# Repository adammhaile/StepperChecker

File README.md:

# StepperChecker

StepperChecker is  a stepper motor driver dev and test board, designed to be easy to build, setup, and use.
It will take any stepstick style motor driver and any Feather compatible microcontroller board.
The basic intent is to have firmware loaded that will move the motor forward or reverse based on which button is pressed, at a sped defined by the potentiometer. But, of course, the sky is the limit given the many Feather boards available.

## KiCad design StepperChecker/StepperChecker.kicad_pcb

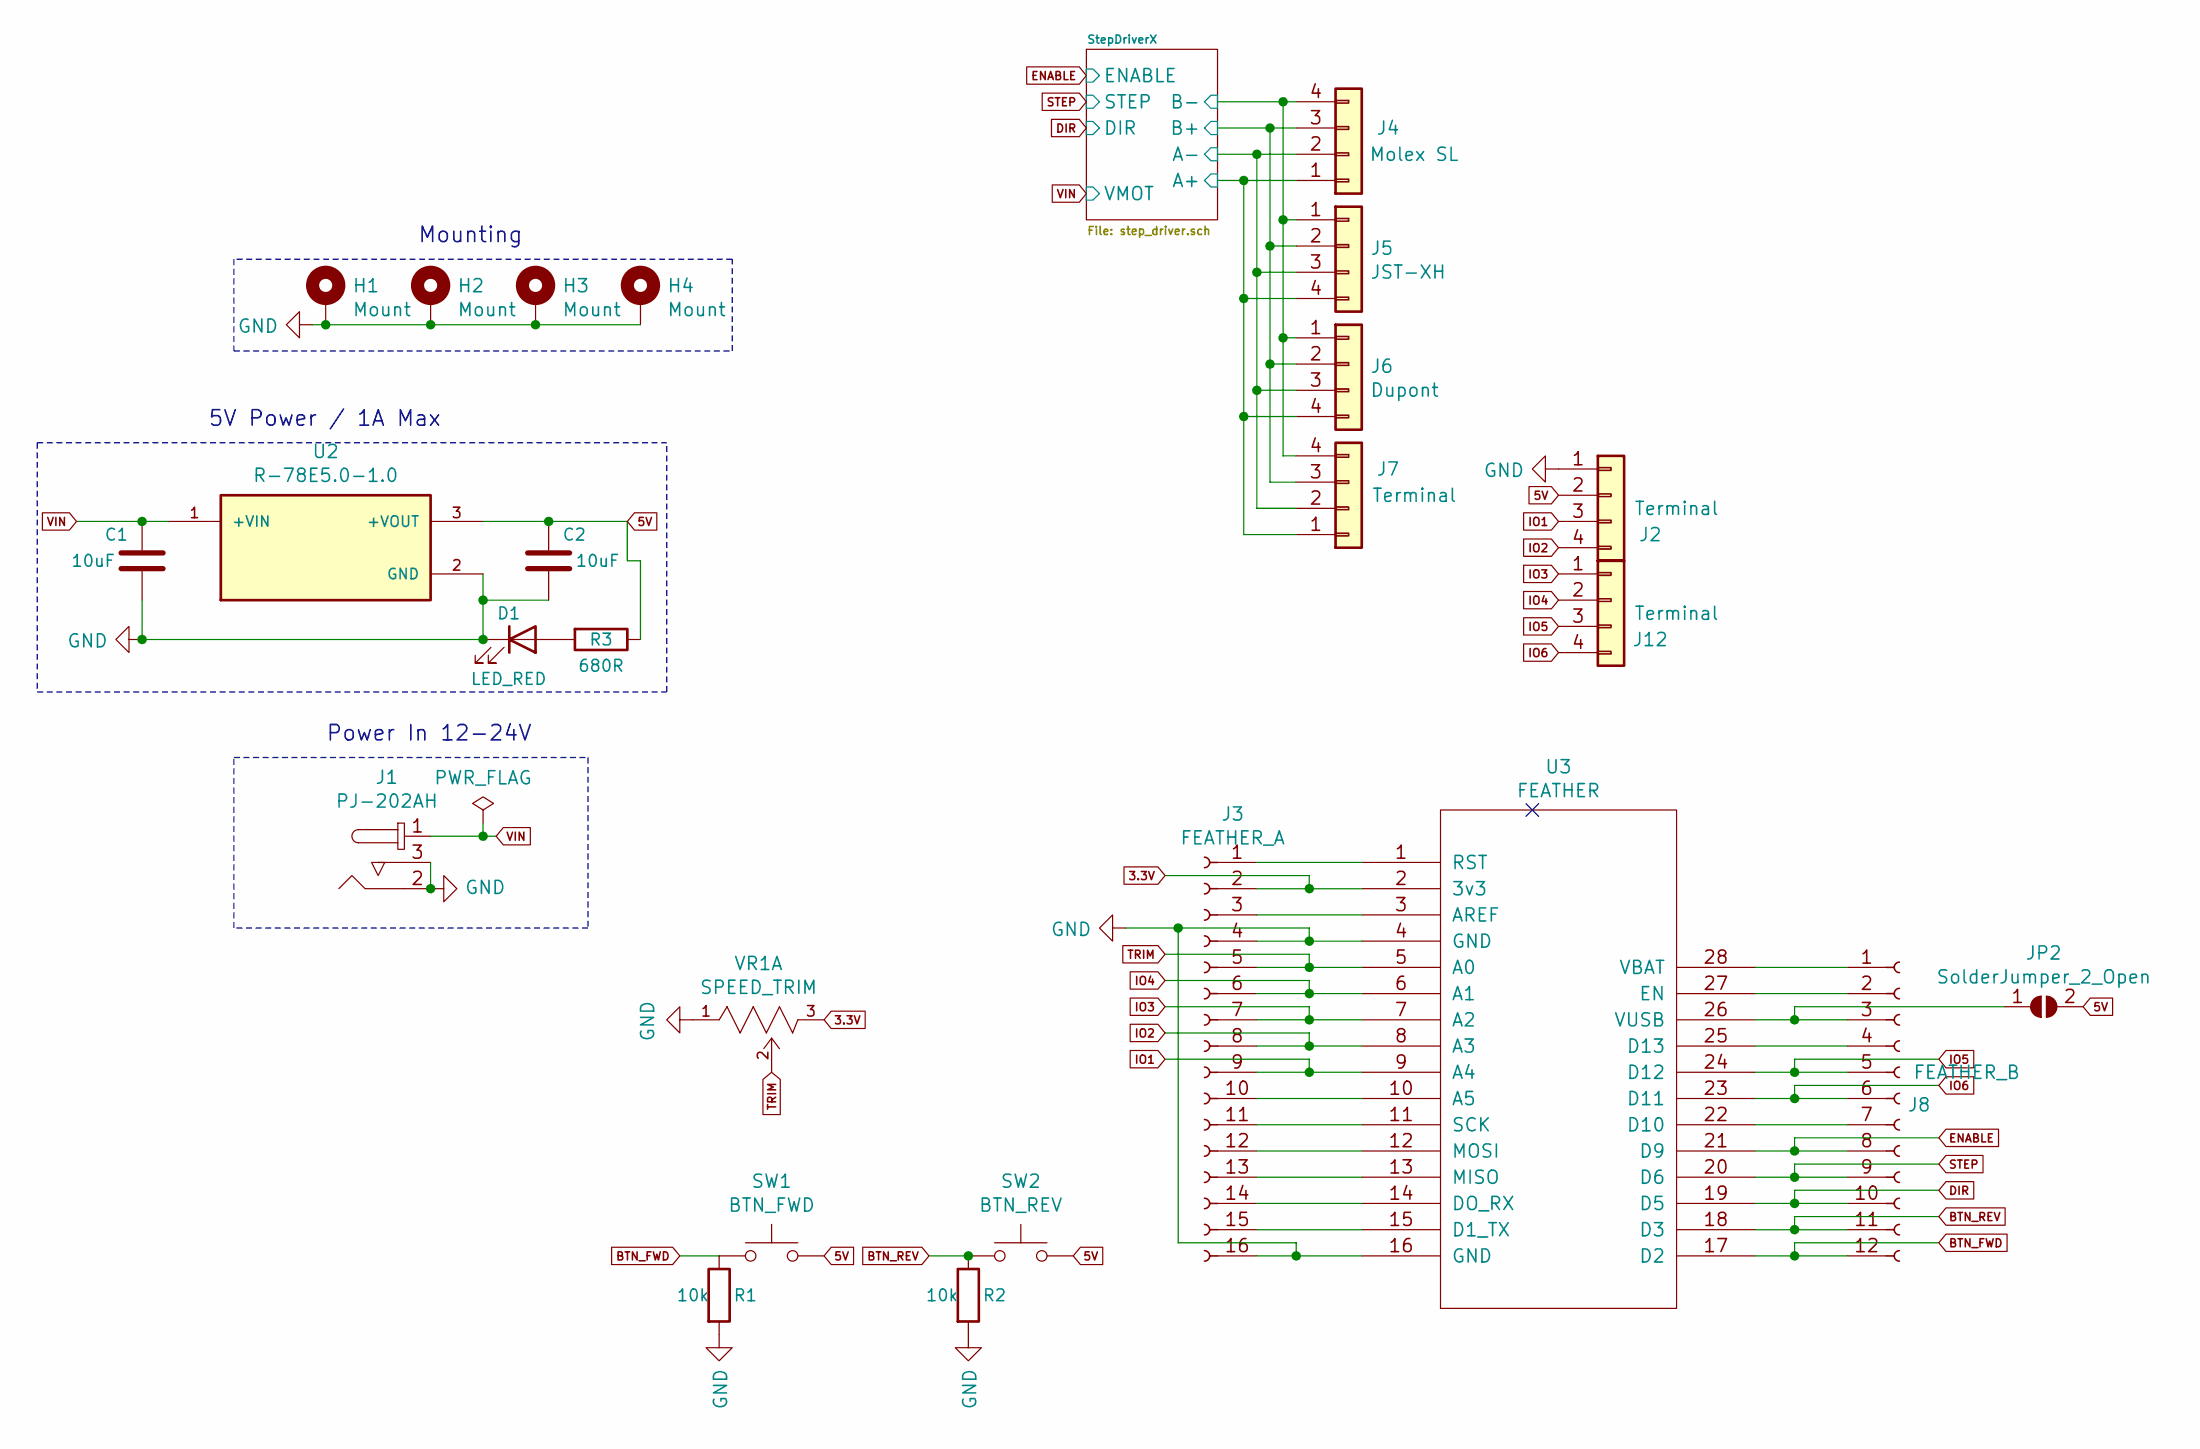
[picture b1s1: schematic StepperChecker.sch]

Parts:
C1, C2: 10uF; CP_Radial_D5.0mm_P2.00mm
D1: LED_RED; LED_D3.0mm
H1, H2, H3, H4: Mount; MountingHole_2.5mm_Pad
J1: PJ-202AH; Barrel_Jack_5.5mmODx2.1mmID_PJ-202A; MPN PJ-202AH; Digi-Key_PN CP-202AH-ND
J2, J7, J12: Terminal; TerminalBlock_Phoenix_MPT-0,5-4-2.54_1x04_P2.54mm_Horizontal
J3: FEATHER_A; PinSocket_1x16_P2.54mm_Vertical
J4: Molex SL; Molex-70543-0038-0-0-MFG
J5: JST-XH; JST_XH_B4B-XH-A_1x04_P2.50mm_Vertical
J6: Dupont; PinHeader_1x04_P2.54mm_Vertical
J8: FEATHER_B; PinSocket_1x12_P2.54mm_Vertical
JP2: SolderJumper_2_Open; SolderJumper-2_P1.3mm_Open_RoundedPad1.0x1.5mm
R1, R2: 10k; R_Axial_DIN0204_L3.6mm_D1.6mm_P7.62mm_Horizontal; MPN RC0603FR-071KL
R3: 680R; R_Axial_DIN0204_L3.6mm_D1.6mm_P7.62mm_Horizontal; MPN RC0603FR-071KL
SW1: BTN_FWD; SW_PUSH_6mm_H5mm
SW2: BTN_REV; SW_PUSH_6mm_H5mm
U2: R-78E5.0-1.0; CONV_R-78E5.0-1.0; PARTREV 6
U3: FEATHER; Adafruit_Feather
VR1: SPEED_TRIM; ALPS-RK09D1130C3W-0; mouser part number 688-RK09D1130C3W

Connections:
3.3V: J3.2, U3.2 (3v3), VR1.3
5V: C2.1, J2.2, JP2.2 (B), R3.1, SW1.2, SW2.2, U2.3 (+VOUT); also elsewhere on the board
/StepDriverX/A+: J4.1, J5.4, J6.4, J7.1; also elsewhere on the board
/StepDriverX/A-: J4.2, J5.3, J6.3, J7.2; also elsewhere on the board
/StepDriverX/B+: J4.3, J5.2, J6.2, J7.3; also elsewhere on the board
/StepDriverX/B-: J4.4, J5.1, J6.1, J7.4; also elsewhere on the board
BTN_FWD: J8.12, R1.1, SW1.1, U3.17 (D2)
BTN_REV: J8.11, R2.1, SW2.1, U3.18 (D3)
DIR: J8.10, U3.19 (D5); also elsewhere on the board
ENABLE: J8.8, U3.21 (D9); also elsewhere on the board
GND: C1.2, C2.2, D1.1 (K), H1.1, H2.1, H3.1, H4.1, J1.2, J1.3, J2.1, J3.4, J3.16, R1.2, R2.2, U2.2 (GND), U3.4 (GND), U3.16 (GND), VR1.1; also elsewhere on the board
IO1: J2.3, J3.9, U3.9 (A4)
IO2: J2.4, J3.8, U3.8 (A3)
IO3: J3.7, J12.1, U3.7 (A2)
IO4: J3.6, J12.2, U3.6 (A1)
IO5: J8.5, J12.3, U3.24 (D12)
IO6: J8.6, J12.4, U3.23 (D11)
unnamed: D1.2 (A), R3.2
unnamed: J3.1, U3.1 (RST)
unnamed: J3.3, U3.3 (AREF)
unnamed: J3.10, U3.10 (A5)
unnamed: J3.11, U3.11 (SCK)
unnamed: J3.12, U3.12 (MOSI)
unnamed: J3.13, U3.13 (MISO)
unnamed: J3.14, U3.14 (DO_RX)
unnamed: J3.15, U3.15 (D1_TX)
unnamed: J8.1, U3.28 (VBAT)
unnamed: J8.2, U3.27 (EN)
unnamed: J8.3, JP2.1 (A), U3.26 (VUSB)
unnamed: J8.4, U3.25 (D13)
unnamed: J8.7, U3.22 (D10)
STEP: J8.9, U3.20 (D6); also elsewhere on the board
TRIM: J3.5, U3.5 (A0), VR1.2
VIN: C1.1, J1.1, U2.1 (+VIN); also elsewhere on the board

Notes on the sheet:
5V Power / 1A Max
Power In 12-24V
Mounting

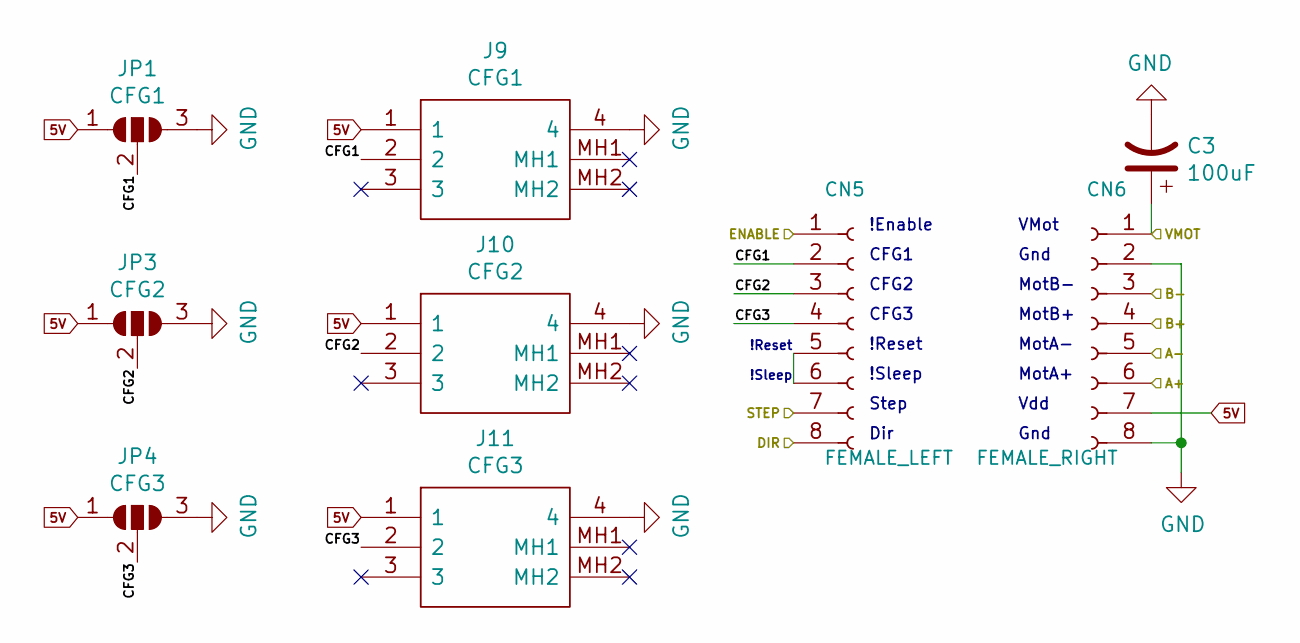
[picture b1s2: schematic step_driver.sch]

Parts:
C3: 100uF; CP_Radial_D8.0mm_P3.50mm
CN5: FEMALE_LEFT; PinSocket_1x08_P2.54mm_Vertical; MPN F185-1108A1BSYC1
CN6: FEMALE_RIGHT; PinSocket_1x08_P2.54mm_Vertical; MPN F185-1108A1BSYC1
J9: CFG1; OS103012MU1QP1; Mouser Part Number 611-OS103012MU1QP1
J10: CFG2; OS103012MU1QP1; Mouser Part Number 611-OS103012MU1QP1
J11: CFG3; OS103012MU1QP1; Mouser Part Number 611-OS103012MU1QP1
JP1: CFG1; SolderJumper-3_P1.3mm_Open_RoundedPad1.0x1.5mm
JP3: CFG2; SolderJumper-3_P1.3mm_Open_RoundedPad1.0x1.5mm
JP4: CFG3; SolderJumper-3_P1.3mm_Open_RoundedPad1.0x1.5mm

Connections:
5V: CN6.7, J9.1, J10.1, J11.1, JP1.1 (A), JP3.1 (A), JP4.1 (A); also elsewhere on the board
/StepDriverX/A+: CN6.6; also elsewhere on the board
/StepDriverX/A-: CN6.5; also elsewhere on the board
/StepDriverX/B+: CN6.4; also elsewhere on the board
/StepDriverX/B-: CN6.3; also elsewhere on the board
/StepDriverX/CFG1: CN5.2, J9.2, JP1.2 (C)
/StepDriverX/CFG2: CN5.3, J10.2, JP3.2 (C)
/StepDriverX/CFG3: CN5.4, J11.2, JP4.2 (C)
DIR: CN5.8; also elsewhere on the board
ENABLE: CN5.1; also elsewhere on the board
GND: C3.2, CN6.2, CN6.8, J9.4, J10.4, J11.4, JP1.3 (B), JP3.3 (B), JP4.3 (B); also elsewhere on the board
unnamed: CN5.5, CN5.6
STEP: CN5.7; also elsewhere on the board
VIN: C3.1, CN6.1; also elsewhere on the board

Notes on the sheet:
!Reset
!Sleep
!Enable
CFG1
CFG2
CFG3
Step
Dir
VMot
Gnd
MotB-
MotB+
MotA-
MotA+
Vdd

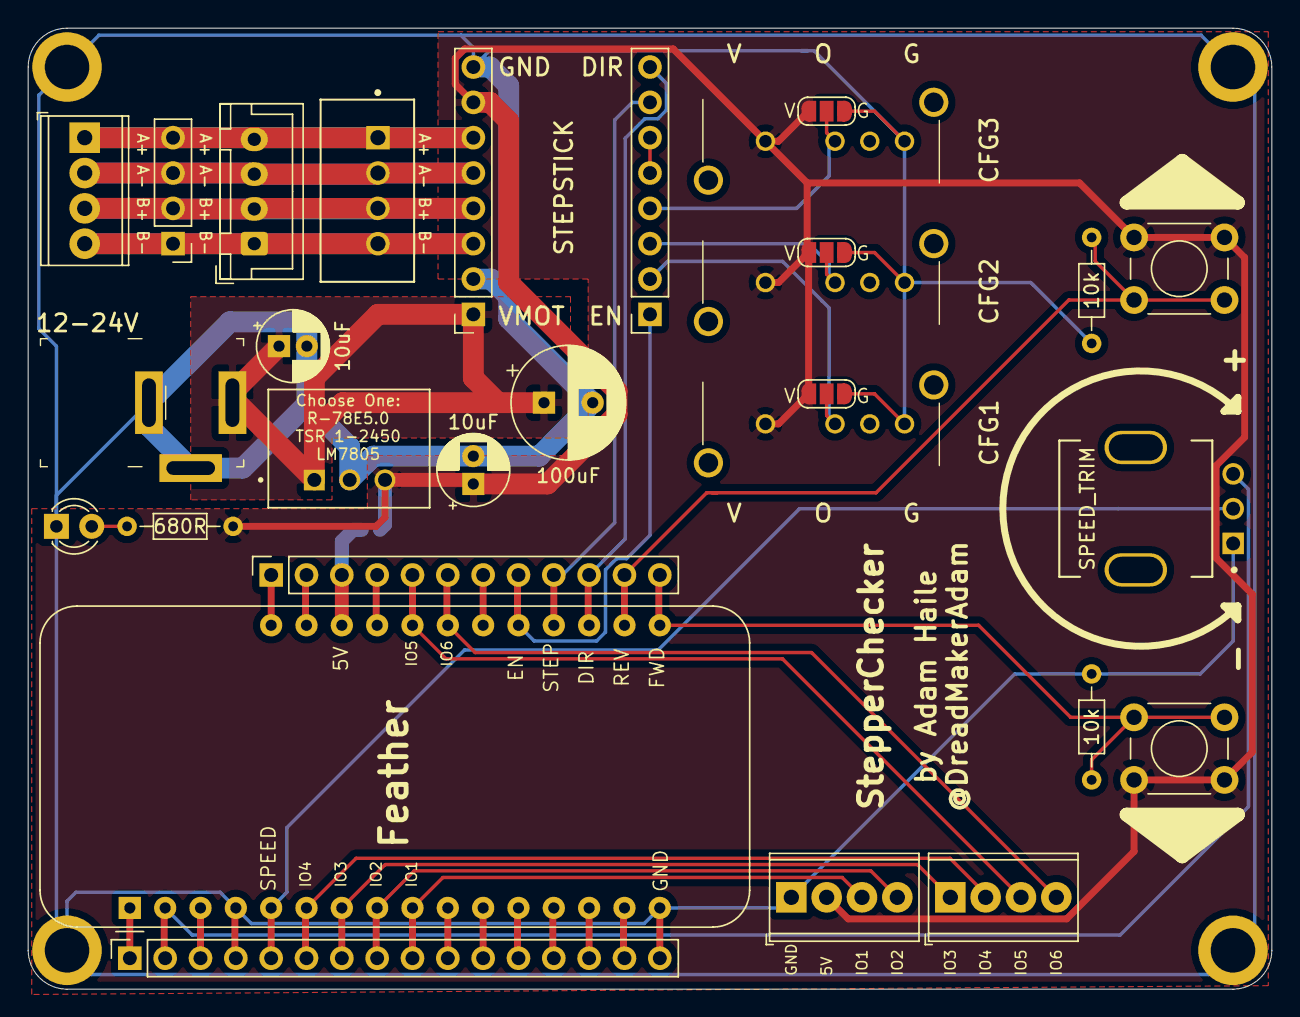
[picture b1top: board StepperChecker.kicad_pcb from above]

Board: 2 copper layers, 89.4 x 69.1 mm, 34 parts (1 on the bottom side), 38 nets.

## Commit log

2021-03-19 Add Recom and jumpers
2021-03-19 Fix missing traces and fill
2021-03-20 Ignore autosave
2021-03-20 updated labels
2021-03-26 Basic firmware test
2021-03-26 Minor board tweaks
